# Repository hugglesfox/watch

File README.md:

# Watch

**(WIP)** A custom motion for the Casio F-91W wrist watch.

While the Casio F-91W is a legendary watch, it doesn't keep time all that well.
Whilst it does boast an impressive 7 year battery life, Casio rates it's
accuracy at ±30 seconds time drift per month. This project aims to design a
replacement PCB for the F-91W which is programmable and temperature
compensated, whilst still retaining a reasonable battery life.

The key goals are:

- \< ±10 seconds of time drift per year
- \> 1 year battery life on a CR2016

## References

Resources and other works which I have referenced for this project

- MSP430FR6972 reference
- https://hackaday.com/2022/02/24/remoticon-2021-joey-castillo-teaches-old-lcds-new-tricks/
- https://github.com/joeycastillo/Sensor-Watch
- https://github.com/carrotIndustries/pluto

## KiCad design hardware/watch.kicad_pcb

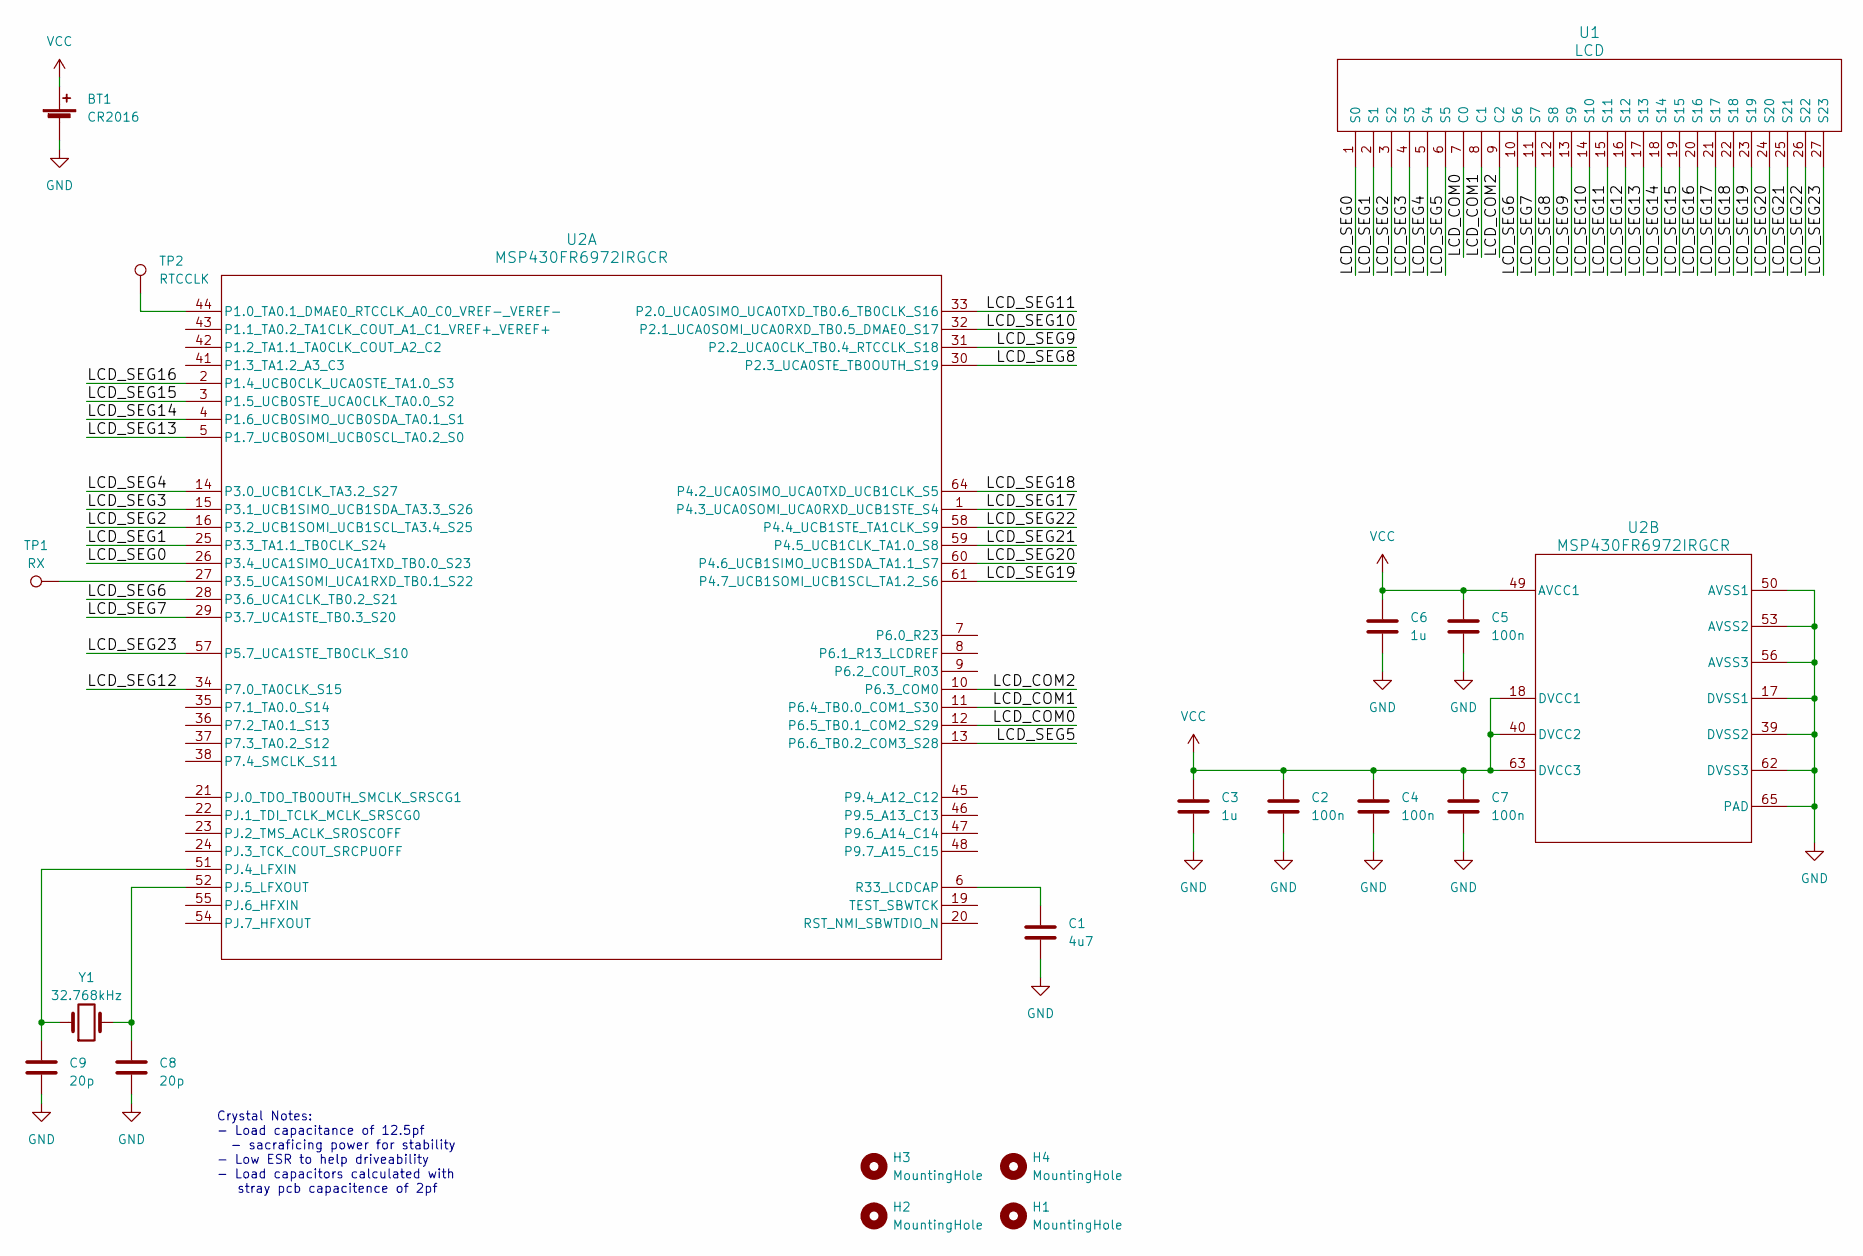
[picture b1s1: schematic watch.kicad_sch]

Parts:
BT1: CR2016; BatteryTerminal
C1: 4u7; C_0402_1005Metric
C2, C4, C5, C7: 100n; C_0402_1005Metric
C3, C6: 1u; C_0402_1005Metric
C8, C9: 20p; C_0402_1005Metric
H1, H2, H3, H4: MountingHole; MountingHole_1.2mm
TP1: RX; TestPoint_Pad_D1.0mm
TP2: RTCCLK; TestPoint_Pad_D1.0mm
U1: LCD
U2: MSP430FR6972IRGCR; RGC0064B_NV
Y1: 32.768kHz; Crystal_SMD_2012-2Pin_2.0x1.2mm

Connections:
/LCD_COM0: U1.7 (C0), U2.12 (P6.5_TB0.1_COM2_S29)
/LCD_COM1: U1.8 (C1), U2.11 (P6.4_TB0.0_COM1_S30)
/LCD_COM2: U1.9 (C2), U2.10 (P6.3_COM0)
/LCD_SEG0: U1.1 (S0), U2.26 (P3.4_UCA1SIMO_UCA1TXD_TB0.0_S23)
/LCD_SEG1: U1.2 (S1), U2.25 (P3.3_TA1.1_TB0CLK_S24)
/LCD_SEG2: U1.3 (S2), U2.16 (P3.2_UCB1SOMI_UCB1SCL_TA3.4_S25)
/LCD_SEG3: U1.4 (S3), U2.15 (P3.1_UCB1SIMO_UCB1SDA_TA3.3_S26)
/LCD_SEG4: U1.5 (S4), U2.14 (P3.0_UCB1CLK_TA3.2_S27)
/LCD_SEG5: U1.6 (S5), U2.13 (P6.6_TB0.2_COM3_S28)
/LCD_SEG6: U1.10 (S6), U2.28 (P3.6_UCA1CLK_TB0.2_S21)
/LCD_SEG7: U1.11 (S7), U2.29 (P3.7_UCA1STE_TB0.3_S20)
/LCD_SEG8: U1.12 (S8), U2.30 (P2.3_UCA0STE_TB0OUTH_S19)
/LCD_SEG9: U1.13 (S9), U2.31 (P2.2_UCA0CLK_TB0.4_RTCCLK_S18)
/LCD_SEG10: U1.14 (S10), U2.32 (P2.1_UCA0SOMI_UCA0RXD_TB0.5_DMAE0_S17)
/LCD_SEG11: U1.15 (S11), U2.33 (P2.0_UCA0SIMO_UCA0TXD_TB0.6_TB0CLK_S16)
/LCD_SEG12: U1.16 (S12), U2.34 (P7.0_TA0CLK_S15)
/LCD_SEG13: U1.17 (S13), U2.5 (P1.7_UCB0SOMI_UCB0SCL_TA0.2_S0)
/LCD_SEG14: U1.18 (S14), U2.4 (P1.6_UCB0SIMO_UCB0SDA_TA0.1_S1)
/LCD_SEG15: U1.19 (S15), U2.3 (P1.5_UCB0STE_UCA0CLK_TA0.0_S2)
/LCD_SEG16: U1.20 (S16), U2.2 (P1.4_UCB0CLK_UCA0STE_TA1.0_S3)
/LCD_SEG17: U1.21 (S17), U2.1 (P4.3_UCA0SOMI_UCA0RXD_UCB1STE_S4)
/LCD_SEG18: U1.22 (S18), U2.64 (P4.2_UCA0SIMO_UCA0TXD_UCB1CLK_S5)
/LCD_SEG19: U1.23 (S19), U2.61 (P4.7_UCB1SOMI_UCB1SCL_TA1.2_S6)
/LCD_SEG20: U1.24 (S20), U2.60 (P4.6_UCB1SIMO_UCB1SDA_TA1.1_S7)
/LCD_SEG21: U1.25 (S21), U2.59 (P4.5_UCB1CLK_TA1.0_S8)
/LCD_SEG22: U1.26 (S22), U2.58 (P4.4_UCB1STE_TA1CLK_S9)
/LCD_SEG23: U1.27 (S23), U2.57 (P5.7_UCA1STE_TB0CLK_S10)
GND: BT1.2 (-), C1.2, C2.2, C3.2, C4.2, C5.2, C6.2, C7.2, C8.2, C9.2, U2.17 (DVSS1), U2.39 (DVSS2), U2.50 (AVSS1), U2.53 (AVSS2), U2.56 (AVSS3), U2.62 (DVSS3), U2.65 (PAD)
unnamed: TP2.1, U2.44 (P1.0_TA0.1_DMAE0_RTCCLK_A0_C0_VREF-_VER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)
unnamed: TP1.1, U2.27 (P3.5_UCA1SOMI_UCA1RXD_TB0.1_S22)
unnamed: C9.1, U2.51 (PJ.4_LFXIN), Y1.1
unnamed: C8.1, U2.52 (PJ.5_LFXOUT), Y1.2
unnamed: C1.1, U2.6 (R33_LCDCAP)
VCC: BT1.1 (+), C2.1, C3.1, C4.1, C5.1, C6.1, C7.1, U2.18 (DVCC1), U2.40 (DVCC2), U2.49 (AVCC1), U2.63 (DVCC3)

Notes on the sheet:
Crystal Notes: - Load capacitance of 12.5pf - sacraficing power for stability - Low ESR to help driveability - Load capacitors calculated with stray pcb capacitence of 2pf

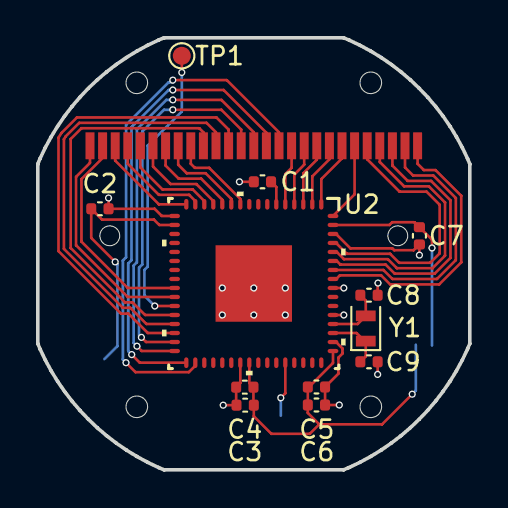
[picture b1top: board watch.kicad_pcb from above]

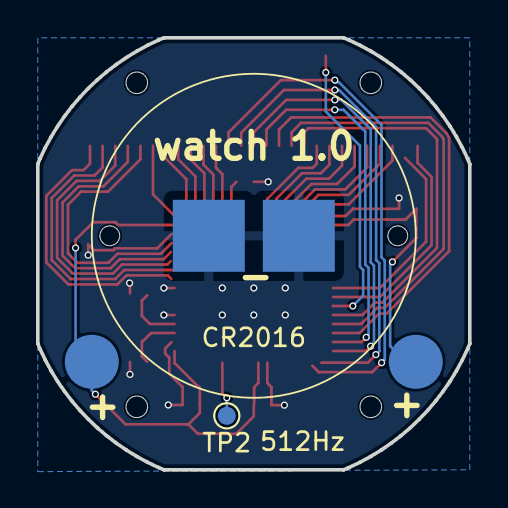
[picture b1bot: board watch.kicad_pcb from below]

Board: 2 copper layers, 24.0 x 24.0 mm, 19 parts (2 on the bottom side), 34 nets.

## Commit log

2023-06-20 Add gitignore
2023-06-20 Add basic readme
2023-06-20 Add basic HAL implementation
2023-06-20 Add initial hardware design
2023-06-20 Add licence
2023-06-21 Fix spelling mistake
2023-06-21 Move .cargo to workspace root
2023-08-13 General hal cleanup
2023-08-15 Add rtc wakeup timer configuration
2023-08-15 Update hal documentation
2023-08-15 Use closures for rtc mode handling
2023-11-10 Move away from state type parameters
2023-11-10 Small cleanup
2023-11-10 Use an integer based segment selection system
2023-11-12 Code cleanup
2024-01-01 Use u16 for alladc calibration values
2024-01-01 Fix ADC calibration dangling pointers
2024-01-03 Make AdcMeaurement functions safe
2024-01-03 Make ADC calibration pointers const
2024-01-19 Switch to stm32l0xx_hal and rtic
2024-01-19 Use Paw Connect for debug connector
2024-01-20 Add buzzer and systick
2024-02-08 Add adc measurements and button handling
2024-02-09 Change to trait based api
2024-02-09 Update footprint library name
2024-03-10 Use git version of stm32-hal
2024-03-10 Update deps
2024-03-10 Move calibration to an infinate task
2024-03-10 Move peripherals to local where possible
2024-04-21 Add kicad to git ignore
2024-04-21 Move to MSP430FR6972 based hardware
2024-04-21 Switch to using MSP430 and C
